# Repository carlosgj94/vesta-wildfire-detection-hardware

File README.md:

# Vesta Fire Detector

Vesta is an early-stage project to build an open source hardware device for
wildfire detection. The hardware design is being done in KiCad, with the goal
of making a device that is easy to manufacture, cheap to deploy, and reliable
in harsh outdoor environments.

The device is intended to detect local environmental changes that may indicate
wildfire risk or an active fire, then report them as early as possible.

## Schematic

## Current Hardware

The current KiCad schematic includes:

- `STM32WL55CCU6`: main low-power microcontroller and wireless reporting
  platform.
- `BQ24074RGTR`: lithium battery charger and power-path management IC.
- `TPS63900DSKR`: efficient buck-boost regulator for the system supply.
- Solar panel inputs and battery connector for field power.
- Crystals, TVS protection, test points, jumpers, and passive support circuitry.

The current sensor set is:

- `BME688`: environmental sensor used for temperature, humidity, pressure, and
  gas/air-quality signals that can help identify smoke or fire-related changes.
- `SHT40-AD1F-R2`: temperature and humidity sensor used for accurate local
  climate readings and cross-checking the environmental baseline.

## Status

The project is still early stage. Full schematics should be ready soon, then the
work will move to PCB layout and 3D CAD. Embedded OS software will be provided
last, once the hardware platform is stable.

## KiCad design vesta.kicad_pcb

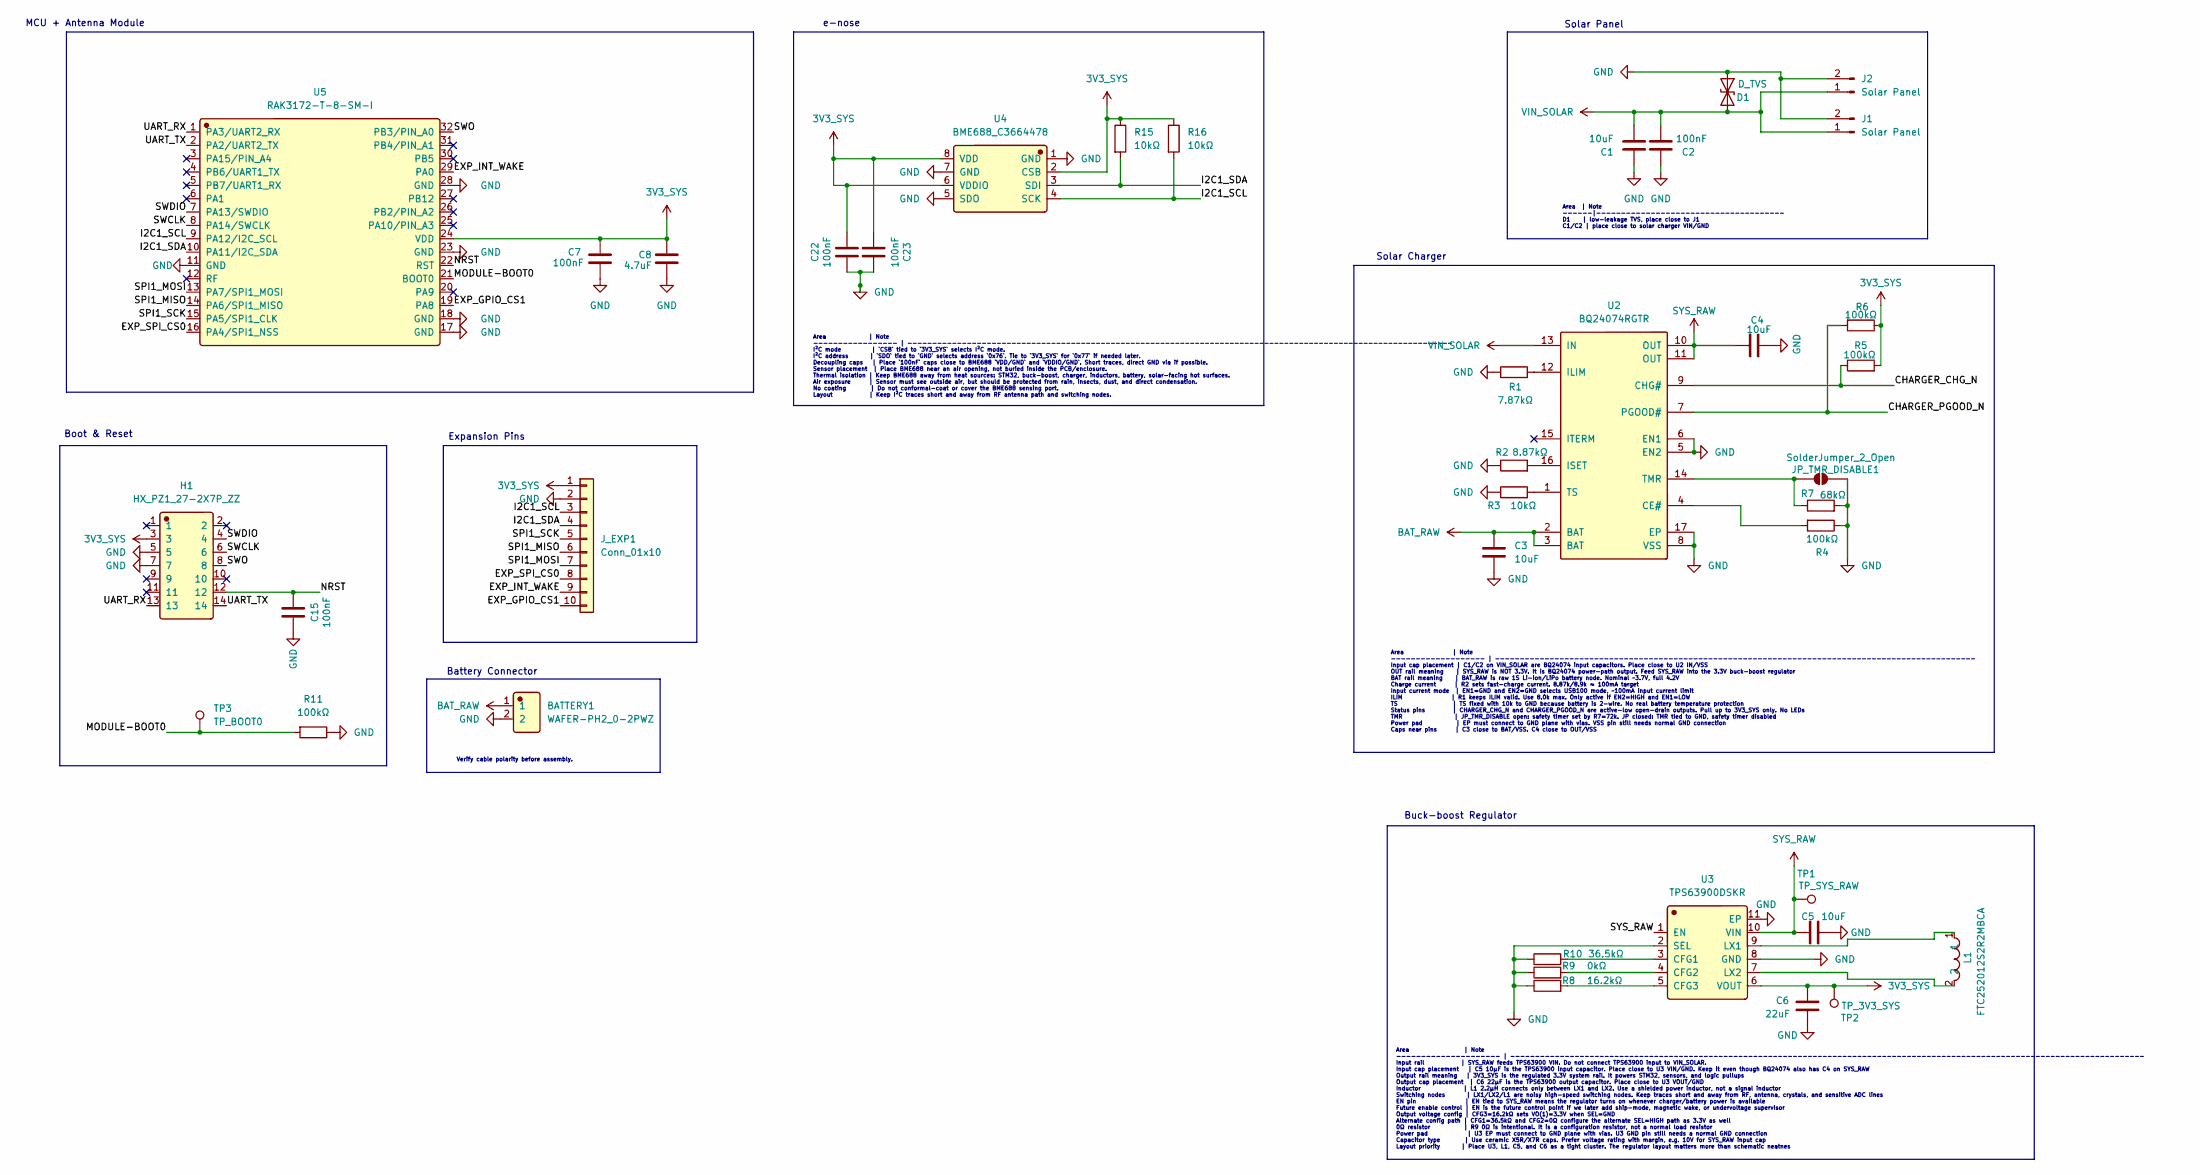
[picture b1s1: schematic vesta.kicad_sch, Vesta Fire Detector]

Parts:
BATTERY1: WAFER-PH2_0-2PWZ; Manufacturer Part WAFER-PH2.0-2PWZ; LCSC C5359610
C1: 10uF; C_0805_2012Metric
C2: 100nF; C_0603_1608Metric
C3, C4, C5: 10uF; C_0805
C6: 22uF; C_0805
C7, C15, C22, C23: 100nF; C_0402_1005Metric
C8: 4.7uF; C_0805_2012Metric
D1: D_TVS; D_SOD-123
H1: HX_PZ1_27-2X7P_ZZ; Manufacturer Part HX PZ1.27-2x7P ZZ; LCSC C22438122
J1, J2: Solar Panel; WAFER-PH2_0-2PWZ
JP_TMR_DISABLE1: SolderJumper_2_Open; SolderJumper-2_P1.3mm_Open_RoundedPad1.0x1.5mm
J_EXP1: Conn_01x10; PinHeader_1x10_P2.00mm_Vertical
L1: FTC252012S2R2MBCA; Manufacturer Part FTC252012S2R2MBCA; LCSC C5832372
R1: 7.87kΩ; R_0603
R2: 8.87kΩ; R_0603
R3, R15, R16: 10kΩ; R_0603
R4, R5, R6: 100kΩ; R_0603
R7: 68kΩ; R_0603
R8: 16.2kΩ; R_0603
R9: 0kΩ; R_0603
R10: 36.5kΩ; R_0603
R11: 100kΩ; R_0402
TP1: TP_SYS_RAW; TestPoint_Pad_D1.5mm
TP2: TP_3V3_SYS; TestPoint_Pad_D1.0mm
TP3: TP_BOOT0; TestPoint_Pad_D1.0mm
U2: BQ24074RGTR; Manufacturer Part BQ24074RGTR; LCSC C54313
U3: TPS63900DSKR; Manufacturer Part TPS63900DSKR; LCSC C1518762
U4: BME688_C3664478; Manufacturer Part BME688; LCSC C3664478
U5: RAK3172-T-8-SM-I; Manufacturer Part RAK3172-T-8-SM-I; LCSC C19723908

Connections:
3V3_SYS: C6.2, C7.2, C8.2, C22.2, C23.2, H1.3, J_EXP1.1, R5.2, R6.1, R15.1, R16.1, TP2.1 (1_1), U3.6 (VOUT), U4.2 (CSB), U4.6 (VDDIO), U4.8 (VDD), U5.24 (VDD)
/CHARGER_CHG_N: R5.1, U2.9 (CHG#)
/CHARGER_PGOOD_N: R6.2, U2.7 (PGOOD#)
/EXP_GPIO_CS1: J_EXP1.10, U5.19 (PA8)
/EXP_INT_WAKE: J_EXP1.9, U5.29 (PA0)
/EXP_SPI_CS0: J_EXP1.8, U5.16 (PA4/SPI1_NSS)
/I2C1_SCL: J_EXP1.3, R16.2, U4.4 (SCK), U5.9 (PA12/I2C_SCL)
/I2C1_SDA: J_EXP1.4, R15.2, U4.3 (SDI), U5.10 (PA11/I2C_SDA)
/MODULE-BOOT0: R11.2, TP3.1 (1_1), U5.21 (BOOT0)
/NRST: C15.1, H1.12, U5.22 (RST)
/SPI1_MISO: J_EXP1.6, U5.14 (PA6/SPI1_MISO)
/SPI1_MOSI: J_EXP1.7, U5.13 (PA7/SPI1_MOSI)
/SPI1_SCK: J_EXP1.5, U5.15 (PA5/SPI1_CLK)
/SWCLK: H1.6, U5.8 (PA14/SWCLK)
/SWDIO: H1.4, U5.7 (PA13/SWDIO)
/SWO: H1.8, U5.32 (PB3/PIN_A0)
/UART_RX: H1.13, U5.1 (PA3/UART2_RX)
/UART_TX: H1.14, U5.2 (PA2/UART2_TX)
BAT_RAW: BATTERY1.1, C3.1, U2.2 (BAT), U2.3 (BAT)
GND: BATTERY1.2, C1.1, C2.1, C3.2, C4.1, C5.1, C6.1, C7.1, C8.1, C15.2, C22.1, C23.1, D1.1 (A1), H1.5, H1.7, J1.2, J2.2, JP_TMR_DISABLE1.2 (B), J_EXP1.2, R1.1, R2.1, R3.1, R4.1, R7.2, R8.1, R9.1, R10.1, R11.1, U2.5 (EN2), U2.6 (EN1), U2.8 (VSS), U2.17 (EP), U3.2 (SEL), U3.8 (GND), U3.11 (EP), U4.1 (GND), U4.5 (SDO), U4.7 (GND), U5.11 (GND), U5.17 (GND), U5.18 (GND), U5.23 (GND), U5.28 (GND); also elsewhere on the board
unnamed 20: JP_TMR_DISABLE1.1 (A), R7.1, U2.14 (TMR); also elsewhere on the board
unnamed: R4.2, U2.4 (CE#)
unnamed: R1.2, U2.12 (ILIM)
unnamed: R2.2, U2.16 (ISET)
unnamed: R3.2, U2.1 (TS)
unnamed: R10.2, U3.3 (CFG1)
unnamed: R9.2, U3.4 (CFG2)
unnamed: R8.2, U3.5 (CFG3)
unnamed: L1.1, U3.9 (LX1)
unnamed: L1.2, U3.7 (LX2)
SYS_RAW: C4.2, C5.2, TP1.1 (1_1), U2.10 (OUT), U2.11 (OUT), U3.1 (EN), U3.10 (VIN)
VIN_SOLAR: C1.2, C2.2, D1.2 (A2), J1.1, J2.1, U2.13 (IN)

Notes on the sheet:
Expansion Pins
e-nose
Area | Note ----------------- | -------------------------------------------------------------------------------------------------------------- I²C mode | `CSB` tied to `3V3_SYS` selects I²C mode. I²C address | `SDO` tied to `GND` selects address `0x76`. Tie to `3V3_SYS` for `0x77` if needed later. 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
MCU + Antenna Module
Buck-boost Regulator
Area | Note --------------------- | -------------------------------------------------------------------------------------------------------------------------------- Input rail | SYS_RAW feeds TPS63900 VIN. Do not connect TPS63900 input to VIN_SOLAR. Input cap placement | C5 10µF is the TPS63900 inp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
Area | Note ------|-------------------------------------- D1 | low-leakage TVS, place close to J1 C1/C2 | place close to solar charger VIN/GND
Solar Charger
Boot & Reset
Verify cable polarity before assembly.
Battery Connector
Solar Panel
Area | Note ------------------- | ------------------------------------------------------------------------------------------------- Input cap placement | C1/C2 on VIN_SOLAR are BQ24074 input capacitors. Place close to U2 IN/VSS OUT rail meaning | SYS_RAW is NOT 3.3V. It is BQ24074 power-path output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

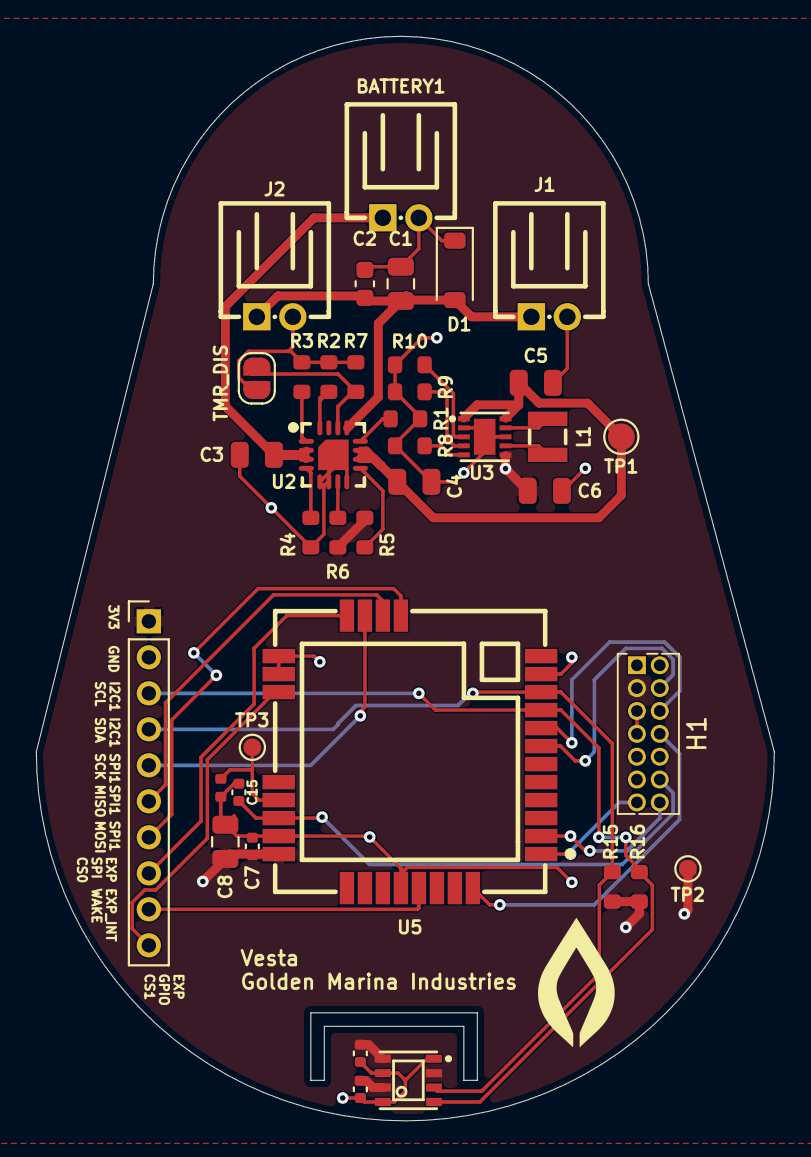
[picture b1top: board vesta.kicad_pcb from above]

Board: 4 copper layers, 41.0 x 60.2 mm, 39 parts (0 on the bottom side), 32 nets.

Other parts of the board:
TMR_DIS: SolderJumper_2_Open; SolderJumper-2_P1.3mm_Open_RoundedPad1.0x1.5mm

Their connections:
GND: TMR_DIS.2 (B); also elsewhere on the board
unnamed 20: TMR_DIS.1 (A); also elsewhere on the board

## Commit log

2026-05-07 feat: initial setup of stm32 and power manangement
2026-05-07 feat: adding the readme
2026-05-07 feat: adding the clocks, the boot and the reset to the schemas
2026-05-08 feat: adding the ST IPD and RF antenna
2026-05-08 feat: adding the connections to the sensor
2026-05-08 feat: adding the expansion pads
2026-05-08 chore: showing the schematics on the readme
2026-05-08 chore: saving backups
2026-05-09 feat: adding all the footprints
2026-05-09 feat: adding the components to the PCB
2026-05-09 feat: making the pinecone
2026-05-11 feat: updating the pins in the stm32 footprint
2026-05-11 feat: created the nets
2026-05-13 feat: doing all the critical connections
2026-05-13 feat: finishing all the connections
2026-05-13 feat: stabilize critical connections
2026-05-13 feat: cleaning the DRC
2026-05-15 feat: improving the thermal dissipation of the sensor
2026-05-16 feat: updating the footprint of the antenna
2026-05-19 feat: updating the references and adding the logo
2026-05-19 feat: updating footprints
2026-05-19 feat: removing unsaved data (no need)
2026-05-19 feat: reverting the polarity on the batteries inputs
2026-05-19 feat: updating the logo to be on the silkscreen
2026-05-20 feat: updating the U.FL part number and generating the gerbers
2026-06-01 feat: changing the MCU and antenna for a pre-certified module
2026-06-01 feat: adding the new components into the PCB
2026-06-02 feat: adding references to all components
2026-06-02 feat: small footprint fixes before starting the routing
2026-06-02 feat: PCB design ready
2026-06-02 feat: updaing the BOM and adding the STLINK connector
2026-06-04 chore: cleaning up the schematics
2026-06-04 feat: small improvements for second revision
